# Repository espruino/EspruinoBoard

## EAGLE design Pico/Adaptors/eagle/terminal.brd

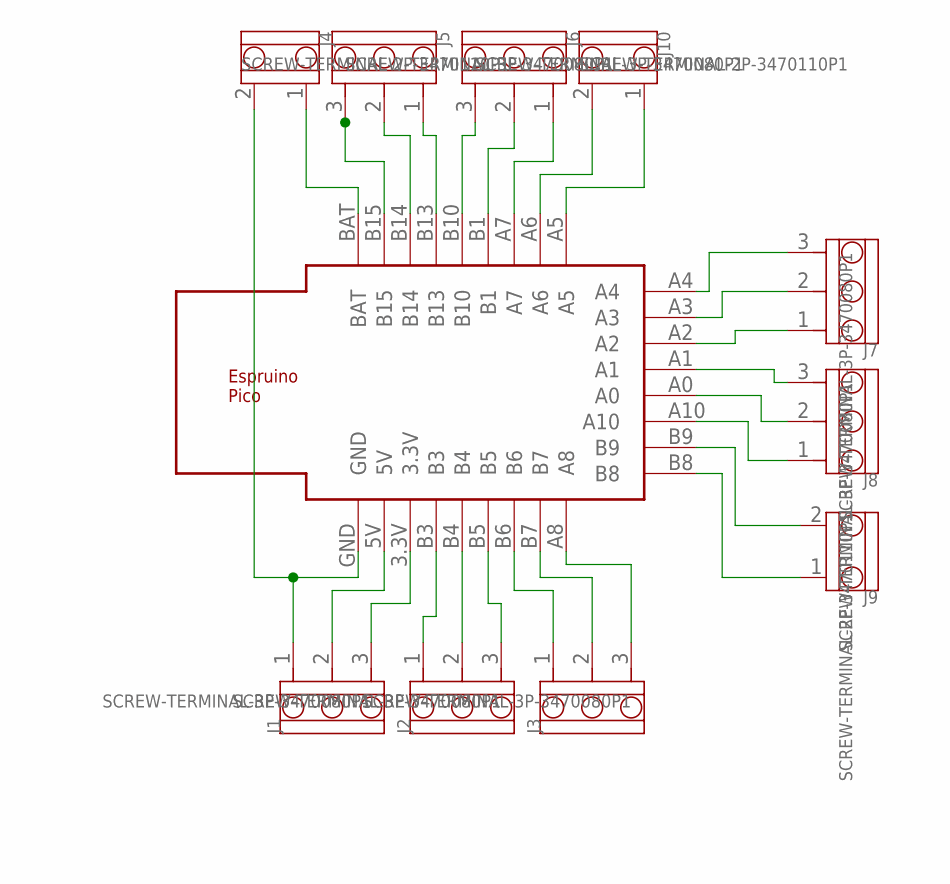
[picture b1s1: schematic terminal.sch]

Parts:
J1, J2, J3, J5, J6, J7, J8: SCREW-TERMINAL-3P-3470080P1; 3P-5.0
J4, J9, J10: SCREW-TERMINAL-2P-3470110P1; 2P-5.0
U$1: ESPRUINO_PICO_SMD

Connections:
unnamed: J4.1, U$1.BAT
unnamed: J5.3, U$1.B15
unnamed: J5.2, U$1.B14
unnamed: J5.1, U$1.B13
unnamed: J6.3, U$1.B10
unnamed: J6.2, U$1.B1
unnamed: J6.1, U$1.A7
unnamed: J10.2, U$1.A6
unnamed: J10.1, U$1.A5
unnamed: J7.3, U$1.A4
unnamed: J7.2, U$1.A3
unnamed: J7.1, U$1.A2
unnamed: J8.3, U$1.A1
unnamed: J8.2, U$1.A0
unnamed: J8.1, U$1.A10
unnamed: J9.2, U$1.B9
unnamed: J9.1, U$1.B8
unnamed: J3.3, U$1.A8
unnamed: J3.2, U$1.B7
unnamed: J3.1, U$1.B6
unnamed: J2.3, U$1.B5
unnamed: J2.2, U$1.B4
unnamed: J2.1, U$1.B3
unnamed: J1.3, U$1.3.3V
unnamed: J1.2, U$1.5V
unnamed: J1.1, J4.2, U$1.GND

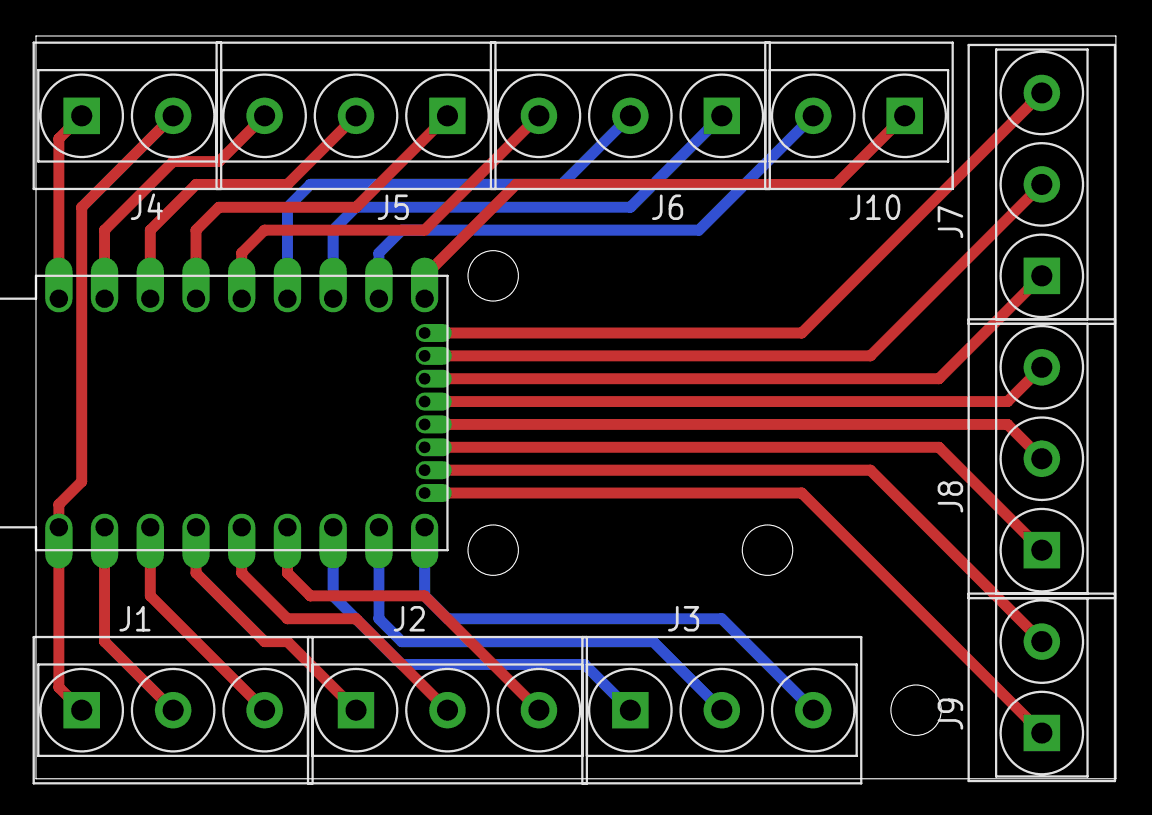
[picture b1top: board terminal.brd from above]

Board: 2 copper layers, 60.0 x 41.3 mm, 11 parts (0 on the bottom side), 26 nets.

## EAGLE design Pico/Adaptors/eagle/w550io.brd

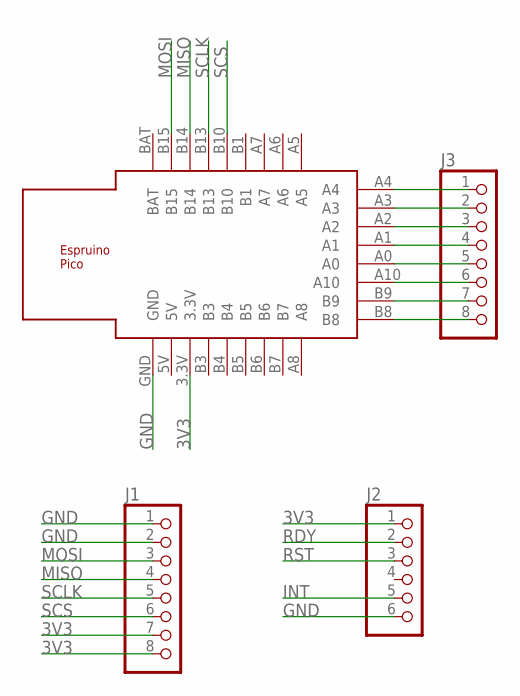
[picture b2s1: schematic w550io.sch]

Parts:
J1, J3: PINHD-1X8; 1X08
J2: PINHD-1X6; 1X06
U$1: ESPRUINO_PICO_SMD

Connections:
3V3: J1.7, J1.8, J2.1, U$1.3.3V
GND: J1.1, J1.2, J2.6, U$1.GND
INT: J2.5
MISO: J1.4, U$1.B14
MOSI: J1.3, U$1.B15
unnamed: J3.1, U$1.A4
unnamed: J3.2, U$1.A3
unnamed: J3.3, U$1.A2
unnamed: J3.4, U$1.A1
unnamed: J3.5, U$1.A0
unnamed: J3.6, U$1.A10
unnamed: J3.7, U$1.B9
unnamed: J3.8, U$1.B8
RDY: J2.2
RST: J2.3
SCLK: J1.5, U$1.B13
SCS: J1.6, U$1.B10

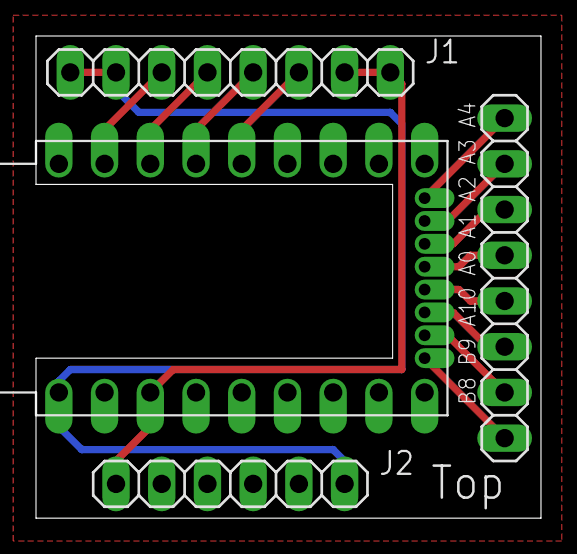
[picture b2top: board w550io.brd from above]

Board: 2 copper layers, 28.1 x 26.8 mm, 4 parts (0 on the bottom side), 14 nets.

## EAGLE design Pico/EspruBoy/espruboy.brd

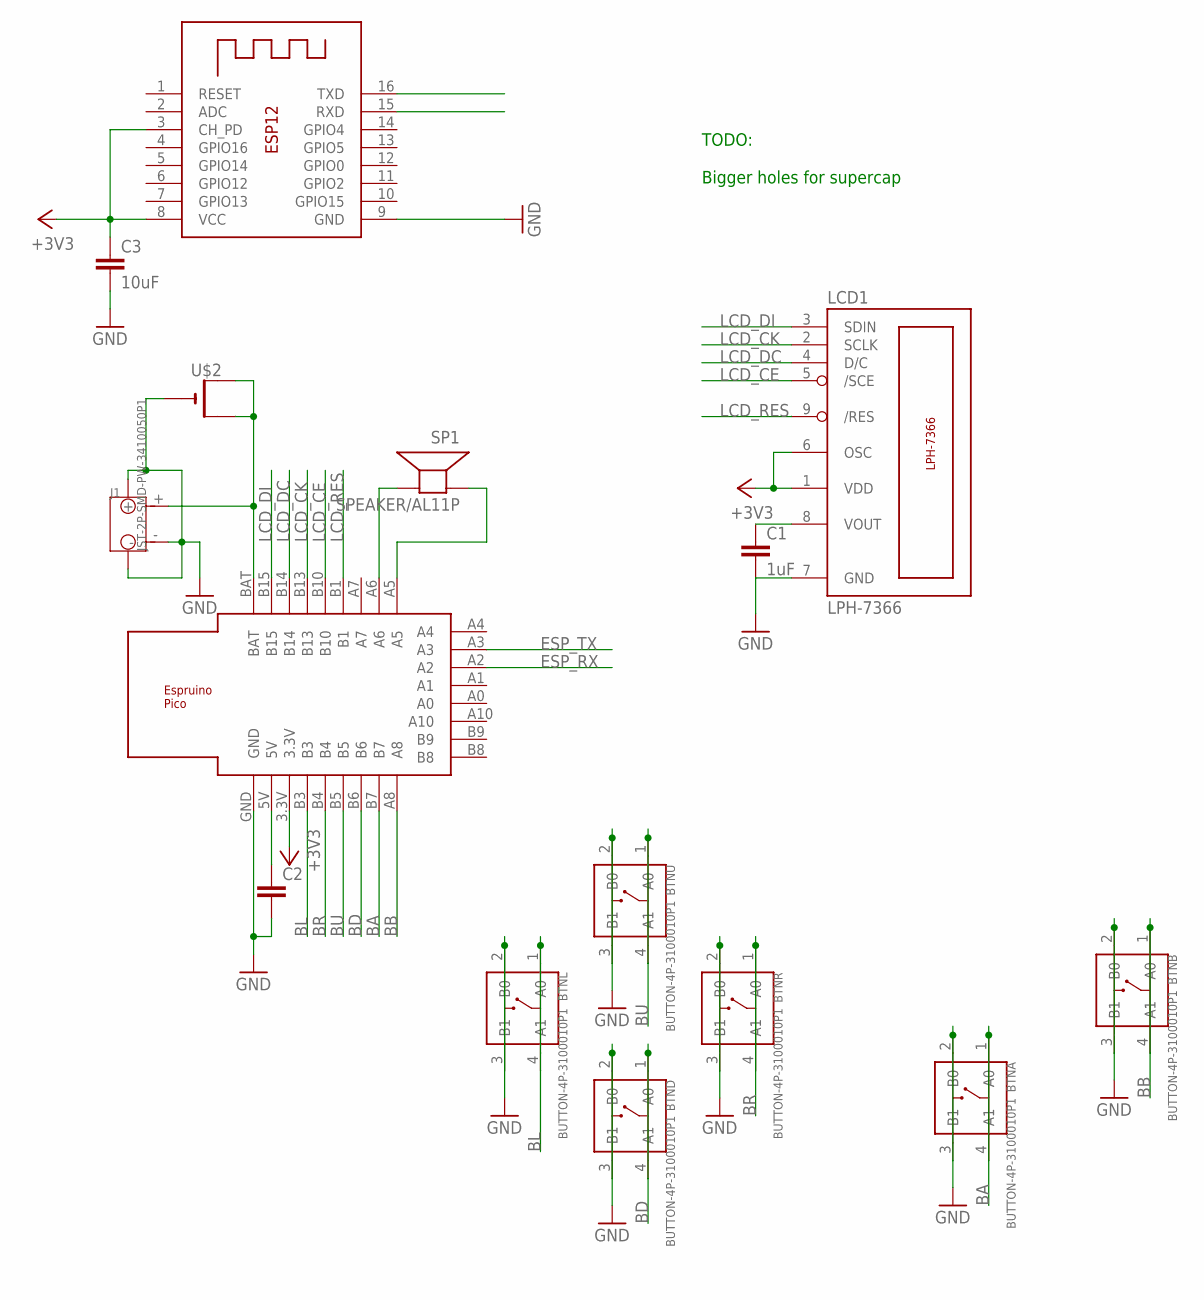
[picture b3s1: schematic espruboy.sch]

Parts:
BTNA: BUTTON-4P-3100010P1; 4P-SMD-6.0X6.0X5.0H
BTNB: BUTTON-4P-3100010P1; 4P-SMD-6.0X6.0X5.0H
BTND: BUTTON-4P-3100010P1; 4P-SMD-6.0X6.0X5.0H
BTNL: BUTTON-4P-3100010P1; 4P-SMD-6.0X6.0X5.0H
BTNR: BUTTON-4P-3100010P1; 4P-SMD-6.0X6.0X5.0H
BTNU: BUTTON-4P-3100010P1; 4P-SMD-6.0X6.0X5.0H
C1: 1uF; C1206
C2: C-EU050-075X075; C050-075X075
C3: 10uF; C1206
ESP12: ESP-12
J1: JST-2P-SMD-PW-3410050P1; 2P-SMD-2.0-90D
LCD1: LPH-7366
SP1: SPEAKER/AL11P; AL11P
U$1: ESPRUINO_PICO_SMDONLY
U$2: CR2032SMT; CR2032-SMD

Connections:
+3V3: C3.1, ESP12.3 (CH_PD), ESP12.8 (VCC), LCD1.1 (VDD), LCD1.6 (OSC), U$1.3.3V
BA: BTNA.1 (A0), BTNA.4 (A1), U$1.B7
BB: BTNB.1 (A0), BTNB.4 (A1), U$1.A8
BD: BTND.1 (A0), BTND.4 (A1), U$1.B6
BL: BTNL.1 (A0), BTNL.4 (A1), U$1.B3
BR: BTNR.1 (A0), BTNR.4 (A1), U$1.B4
BU: BTNU.1 (A0), BTNU.4 (A1), U$1.B5
ESP_RX: ESP12.15 (RXD), U$1.A2
ESP_TX: ESP12.16 (TXD), U$1.A3
GND: BTNA.2 (B0), BTNA.3 (B1), BTNB.2 (B0), BTNB.3 (B1), BTND.2 (B0), BTND.3 (B1), BTNL.2 (B0), BTNL.3 (B1), BTNR.2 (B0), BTNR.3 (B1), BTNU.2 (B0), BTNU.3 (B1), C1.2, C2.2, C3.2, ESP12.9 (GND), J1.3, J1.4, J1.-, LCD1.7 (GND), U$1.GND, U$2.-
LCD_CE: LCD1.5 (/SCE), U$1.B10
LCD_CK: LCD1.2 (SCLK), U$1.B13
LCD_DC: LCD1.4 (D/C), U$1.B14
LCD_DI: LCD1.3 (SDIN), U$1.B15
LCD_RES: LCD1.9 (/RES), U$1.B1
unnamed: C1.1, LCD1.8 (VOUT)
unnamed: J1.+, U$1.BAT, U$2.+$1 (+), U$2.+$2 (+1)
unnamed: C2.1, U$1.5V
unnamed: SP1.-, U$1.A6
unnamed: SP1.+, U$1.A5

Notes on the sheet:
TODO: Bigger holes for supercap

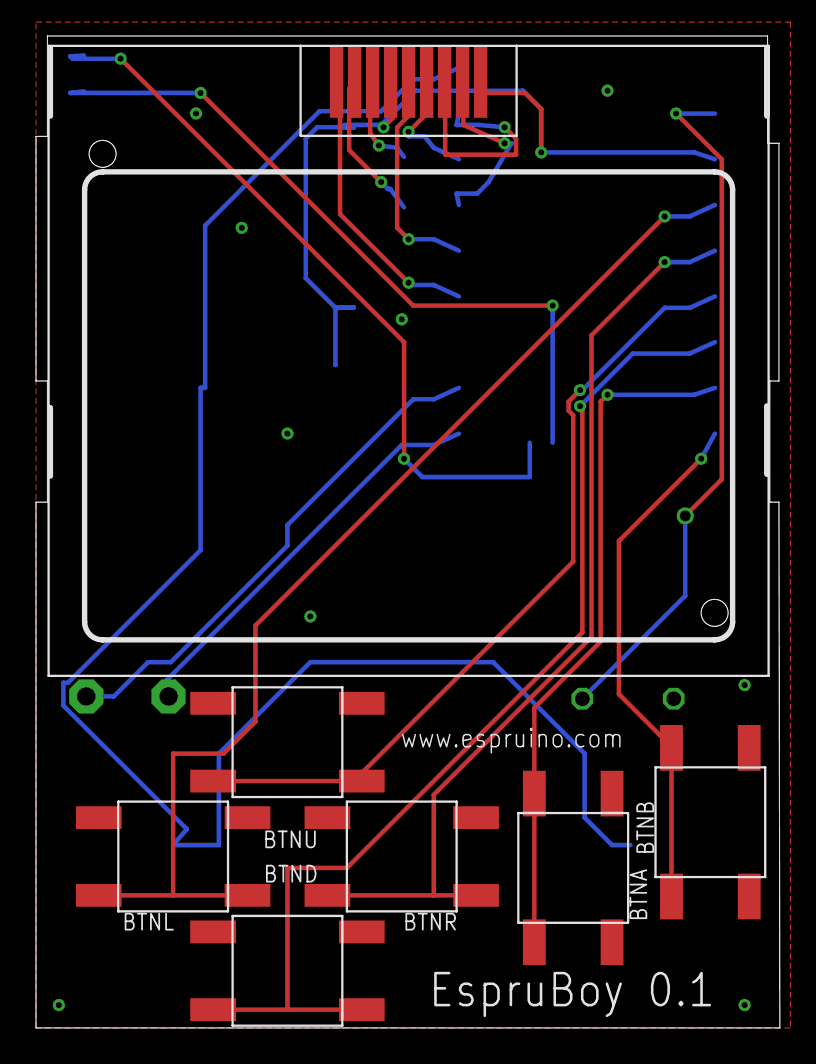
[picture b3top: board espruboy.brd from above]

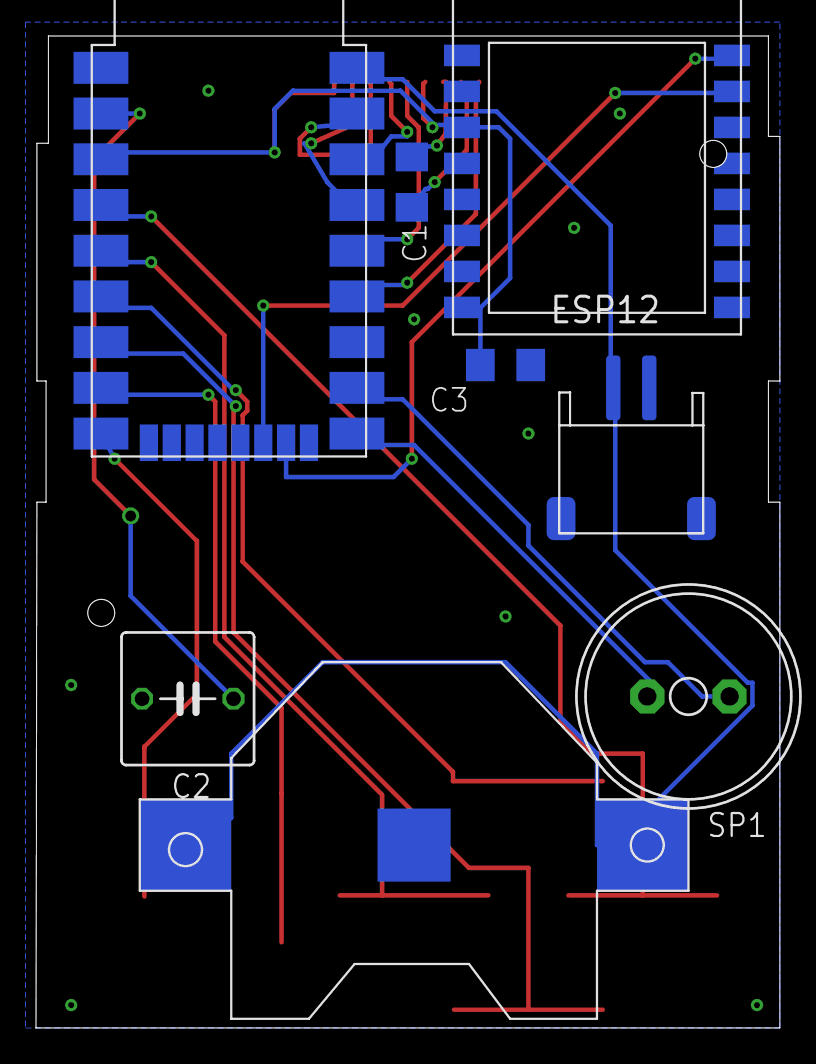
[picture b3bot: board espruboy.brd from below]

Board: 2 copper layers, 41.3 x 55.1 mm, 15 parts (8 on the bottom side), 20 nets.

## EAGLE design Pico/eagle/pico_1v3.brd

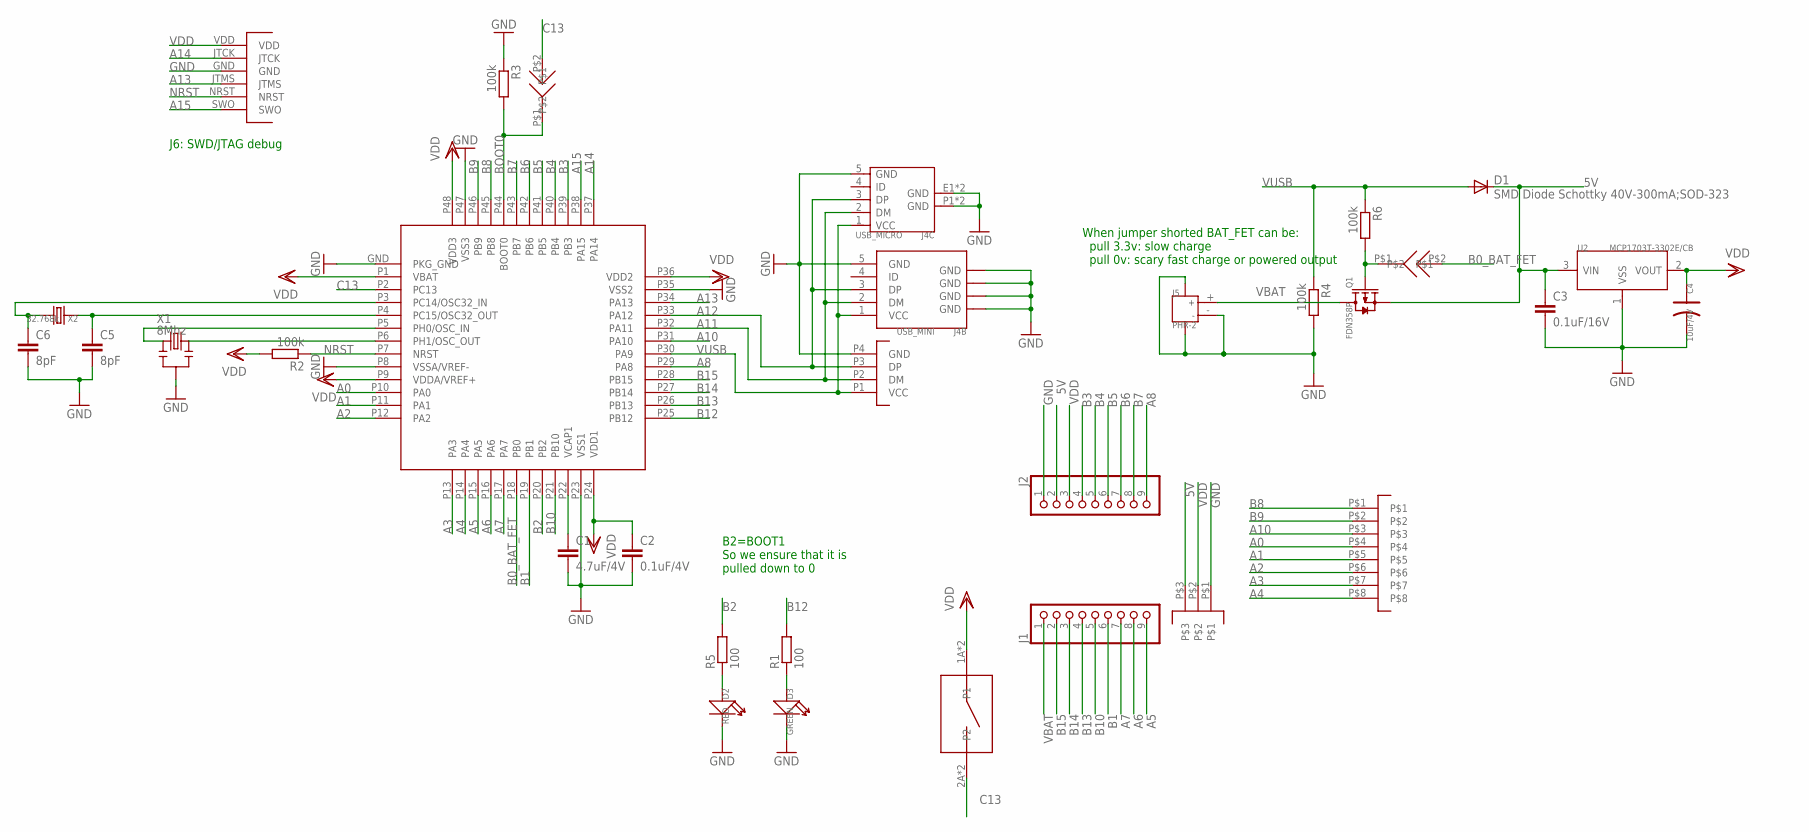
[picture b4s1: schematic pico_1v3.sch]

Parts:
B1: KMR421NG
C1: 4.7uF/4V; C0402
C2: 0.1uF/4V; C0402
C3: 0.1uF/16V; C0402
C4: 10uF/4V; AVX-A
C5, C6: 8pF; C0402
D1: SMD Diode Schottky 40V-300mA;SOD-323; SOD323-W
D2: RED; LED-0402
D3: GREEN; LED-0402
J1, J2: PINHEAD9
J3, J7: SOLDERJUMPER
J4A: USB_TYPE_A_ONBOARD; USB_TYPEA_ONBOARD
J4B: USB_MINI
J4C: USB_MICRO
J5: PHR-2; JST-SMD-2.0-90D
J6: CON-SWD
J8: PINHEAD-1.27-8X1
J9: PINHEAD-1.27-3X1
Q1: FDN358P; SOT23
R1, R5: 100; R0402
R2, R3, R4, R6: 100k; R0402
U1: STM32F401CDU6; UFQFPN48
U2: MCP1703T-3302E/CB; SOT23
X1: 8Mhz; 3P-SMD-3.6X1.3
X2: 32.768k; 2P-SMD-2.05X1.2

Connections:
5V: C3.1, D1.C, J2.2, J9.P$3, Q1.2 (S), U2.3 (VIN)
A0: J8.P$4, U1.P10 (PA0)
A1: J8.P$5, U1.P11 (PA1)
A2: J8.P$6, U1.P12 (PA2)
A3: J8.P$7, U1.P13 (PA3)
A4: J8.P$8, U1.P14 (PA4)
A5: J1.9, U1.P15 (PA5)
A6: J1.8, U1.P16 (PA6)
A7: J1.7, U1.P17 (PA7)
A8: J2.9, U1.P29 (PA8)
A10: J8.P$3, U1.P31 (PA10)
A11: J4A.P2 (DM), J4B.2 (DM), J4C.2 (DM), U1.P32 (PA11)
A12: J4A.P3 (DP), J4B.3 (DP), J4C.3 (DP), U1.P33 (PA12)
A13: J6.JTMS, U1.P34 (PA13)
A14: J6.JTCK, U1.P37 (PA14)
A15: J6.SWO, U1.P38 (PA15)
B0_BAT_FET: J3.P$2, U1.P18 (PB0)
B1: J1.6, U1.P19 (PB1)
B2: R5.2, U1.P20 (PB2)
B3: J2.4, U1.P39 (PB3)
B4: J2.5, U1.P40 (PB4)
B5: J2.6, U1.P41 (PB5)
B6: J2.7, U1.P42 (PB6)
B7: J2.8, U1.P43 (PB7)
B8: J8.P$1, U1.P45 (PB8)
B9: J8.P$2, U1.P46 (PB9)
B10: J1.5, U1.P21 (PB10)
B12: R1.2, U1.P25 (PB12)
B13: J1.4, U1.P26 (PB13)
B14: J1.3, U1.P27 (PB14)
B15: J1.2, U1.P28 (PB15)
BOOT0: J7.P$1, R3.2, U1.P44 (BOOT0)
C13: B1.2A (P2), B1.2B (P2), J7.P$2, U1.P2 (PC13)
GND: C1.2, C2.2, C3.2, C4.- (2), C5.2, C6.2, D2.-, D3.-, J2.1, J4A.P4 (GND), J4B.5 (GND), J4B.P$1 (GND), J4B.P$2 (GND), J4B.P$3 (GND), J4B.P$4 (GND), J4C.5 (GND), J4C.E1 (GND), J4C.E2 (GND), J4C.P1 (GND), J4C.P2 (GND), J5.3, J5.4, J5.- (2), J6.GND, J9.P$1, R3.1, R4.2, U1.GND (PKG_GND), U1.P8 (VSSA/VREF-), U1.P23 (VSS1), U1.P35 (VSS2), U1.P47 (VSS3), U2.1 (VSS), X1.2
unnamed: C5.1, U1.P4 (PC15/OSC32_OUT), X2.1
unnamed: C6.1, U1.P3 (PC14/OSC32_IN), X2.2
unnamed: U1.P5 (PH0/OSC_IN), X1.1
unnamed: U1.P6 (PH1/OSC_OUT), X1.3
unnamed: D2.+, R5.1
unnamed: D3.+, R1.1
unnamed: J3.P$1, Q1.1 (G), R6.2
unnamed: C1.1, U1.P22 (VCAP1)
NRST: J6.NRST, R2.1, U1.P7 (NRST)
VBAT: J1.1, J5.+ (1), Q1.3 (D)
VDD: B1.1A (P1), B1.1B (P1), C2.1, C4.+ (1), J2.3, J6.VDD, J9.P$2, R2.2, U1.P1 (VBAT), U1.P9 (VDDA/VREF+), U1.P24 (VDD1), U1.P36 (VDD2), U1.P48 (VDD3), U2.2 (VOUT)
VUSB: D1.A, J4A.P1 (VCC), J4B.1 (VCC), J4C.1 (VCC), R4.1, R6.1, U1.P30 (PA9)

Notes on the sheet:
When jumper shorted BAT_FET can be: pull 3.3v: slow charge pull 0v: scary fast charge or powered output
B2=BOOT1 So we ensure that it is pulled down to 0
J6: SWD/JTAG debug

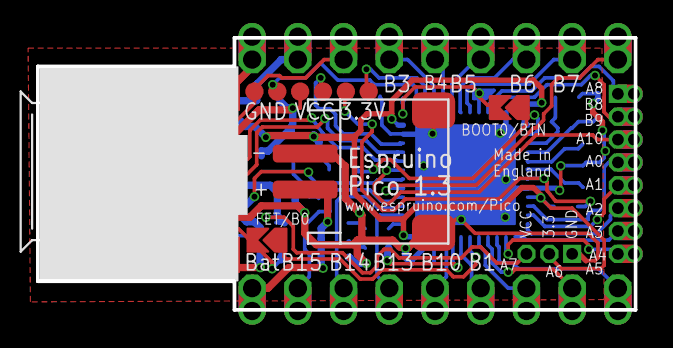
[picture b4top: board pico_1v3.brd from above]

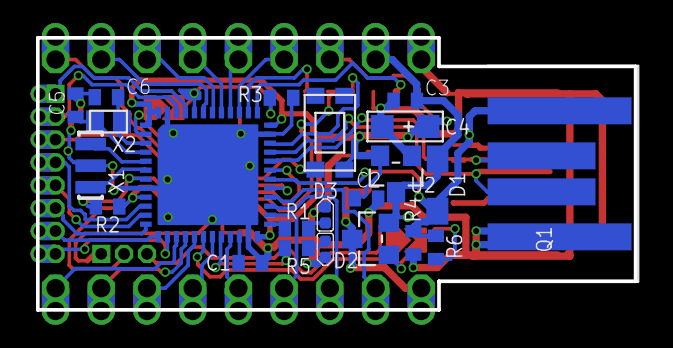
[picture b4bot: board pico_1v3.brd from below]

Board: 2 copper layers, 33.2 x 15.1 mm, 32 parts (22 on the bottom side), 46 nets.
